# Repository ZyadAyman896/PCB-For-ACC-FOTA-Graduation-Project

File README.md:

# PCB-For-ACC-FOTA-Graduation-Project
My PCB design for our graduation's project .
## PCB Fabricated

### PCB Design

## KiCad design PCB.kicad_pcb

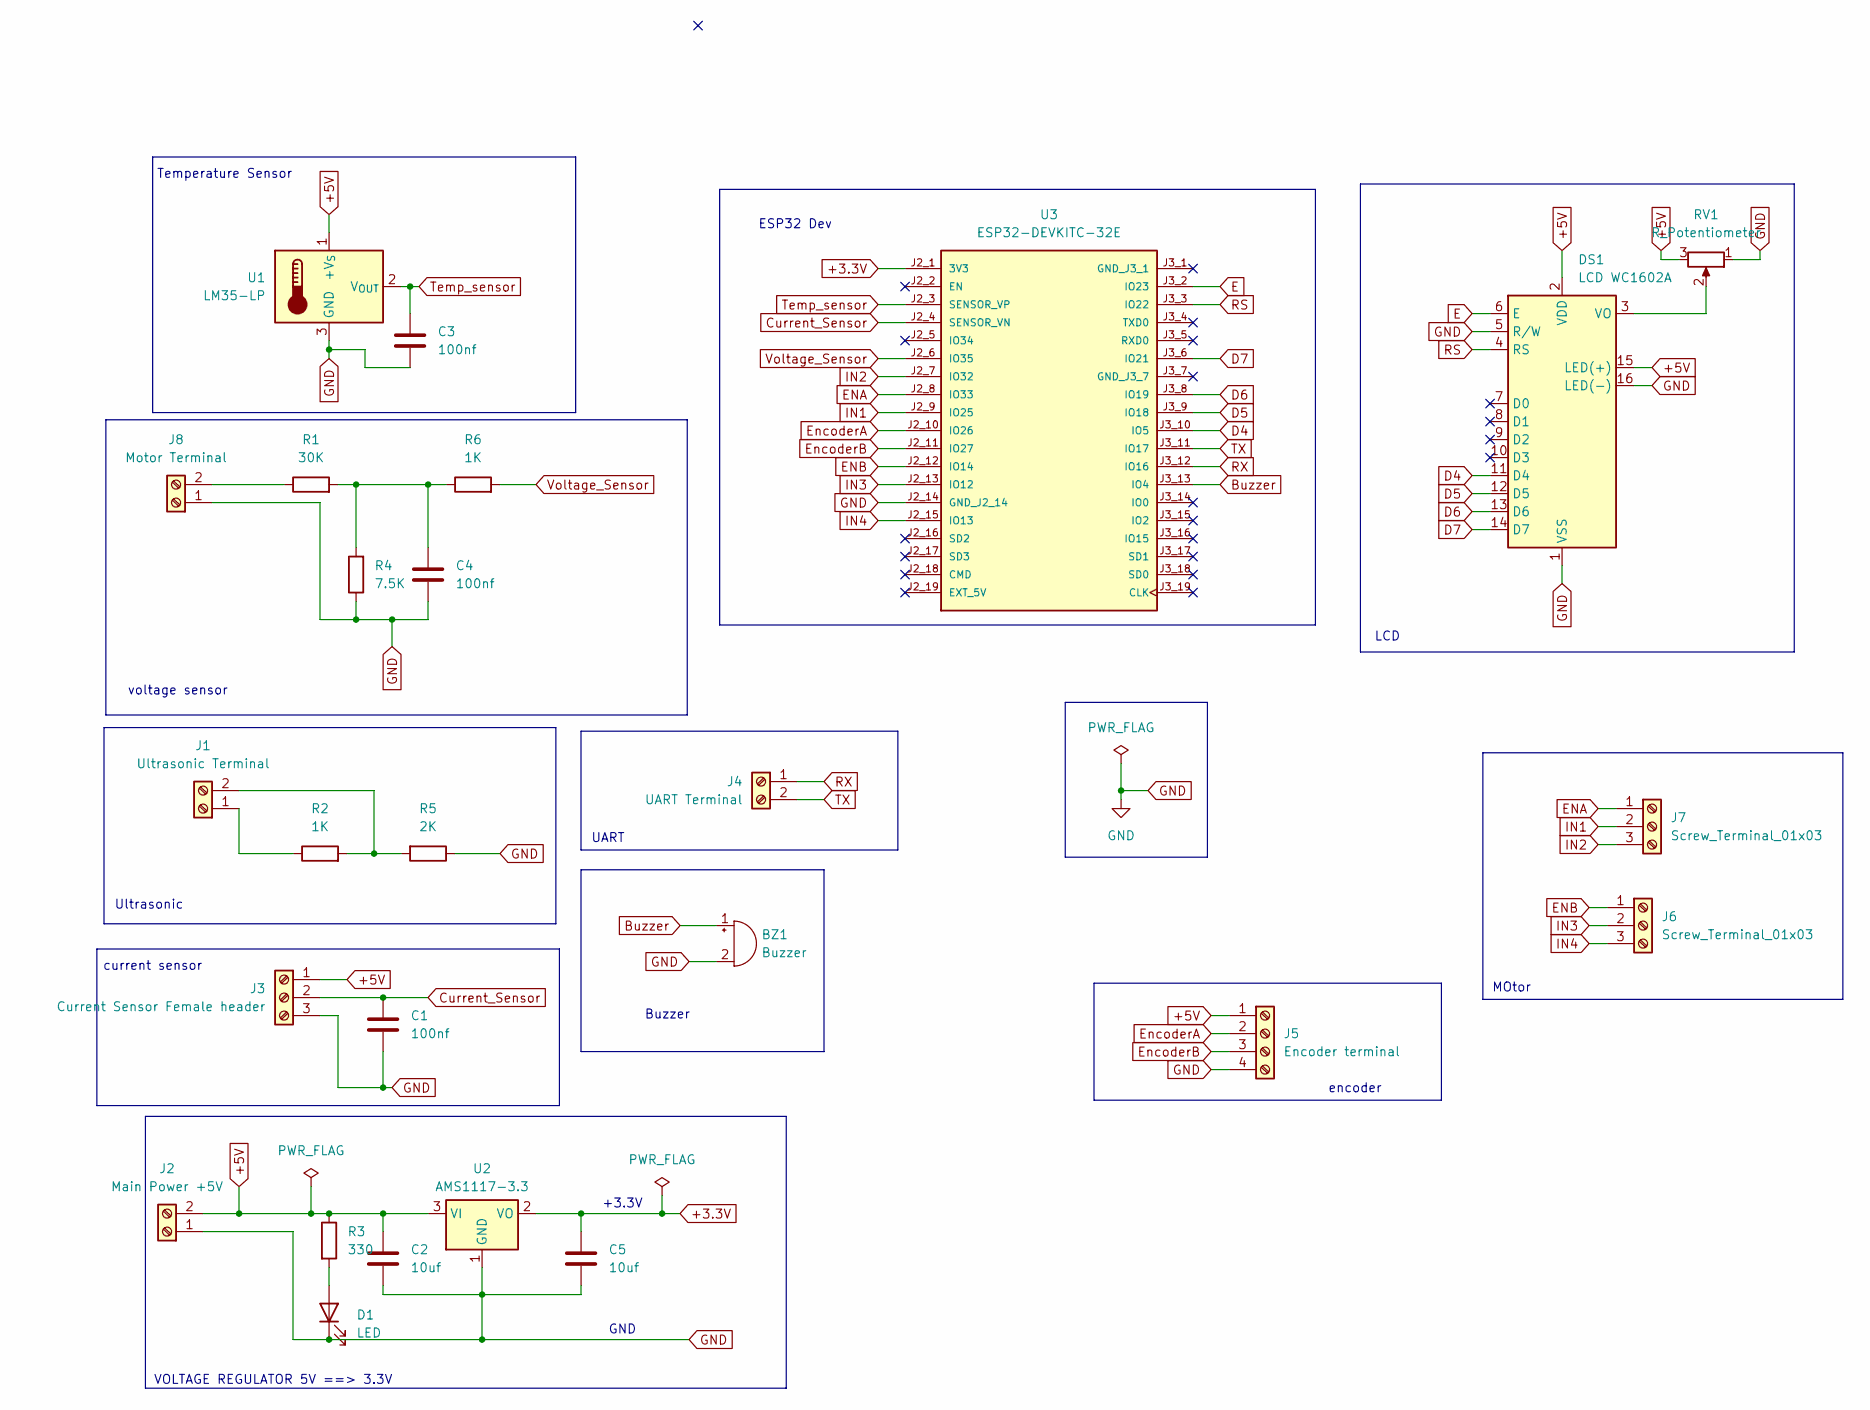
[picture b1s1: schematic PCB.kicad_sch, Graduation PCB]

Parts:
BZ1: Buzzer; Buzzer_12x9.5RM7.6
C1, C3, C4: 100nf; C_Disc_D5.0mm_W2.5mm_P5.00mm
C2, C5: 10uf; CP_Radial_D5.0mm_P2.00mm
D1: LED; LED_1206_3216Metric
DS1: LCD WC1602A; PinHeader_1x16_P2.54mm_Vertical
J1: Ultrasonic Terminal; TerminalBlock_bornier-2_P5.08mm
J2: Main Power +5V; TerminalBlock_bornier-2_P5.08mm
J3: Current Sensor Female header; PinHeader_1x03_P2.54mm_Vertical
J4: UART Terminal; TerminalBlock_bornier-2_P5.08mm
J5: Encoder terminal; TE_282837-4
J6, J7: Screw_Terminal_01x03; TE_282836-3
J8: Motor Terminal; TerminalBlock_bornier-2_P5.08mm
R1: 30K; R_Axial_DIN0207_L6.3mm_D2.5mm_P10.16mm_Horizontal
R2, R6: 1K; R_Axial_DIN0207_L6.3mm_D2.5mm_P10.16mm_Horizontal
R3: 330; R_Axial_DIN0207_L6.3mm_D2.5mm_P10.16mm_Horizontal
R4: 7.5K; R_Axial_DIN0207_L6.3mm_D2.5mm_P10.16mm_Horizontal
R5: 2K; R_Axial_DIN0207_L6.3mm_D2.5mm_P10.16mm_Horizontal
RV1: R_Potentiometer; TRIM_WH148-1A-2-18T-L20
U1: LM35-LP; TO-92_Inline
U2: AMS1117-3.3; SOT-223-3_TabPin2
U3: ESP32-DEVKITC-32E; MODULE_ESP32-DEVKITC-32E; PARTREV 1.4

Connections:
+3.3V: C5.1, U2.2 (VO), U3.J2_1 (3V3)
+5V: C2.1, DS1.2 (VDD), DS1.15 (LED(+)), J2.2, J3.1, J5.1, R3.1, RV1.3, U1.1 (+V_{S}), U2.3 (VI)
Buzzer: BZ1.1 (+), U3.J3_13 (IO4)
Current_Sensor: C1.1, J3.2, U3.J2_4 (SENSOR_VN)
D4: DS1.11 (D4), U3.J3_10 (IO5)
D5: DS1.12 (D5), U3.J3_9 (IO18)
D6: DS1.13 (D6), U3.J3_8 (IO19)
D7: DS1.14 (D7), U3.J3_6 (IO21)
E: DS1.6 (E), U3.J3_2 (IO23)
ENA: J7.1, U3.J2_8 (IO33)
ENB: J6.1, U3.J2_12 (IO14)
EncoderA: J5.2, U3.J2_10 (IO26)
EncoderB: J5.3, U3.J2_11 (IO27)
GND: BZ1.2 (-), C1.2, C2.2, C3.2, C4.2, C5.2, D1.1 (K), DS1.1 (VSS), DS1.5 (R/W), DS1.16 (LED(-)), J2.1, J3.3, J5.4, J8.1, R4.1, R5.1, RV1.1, U1.3 (GND), U2.1 (GND), U3.J2_14 (GND_J2_14)
IN1: J7.2, U3.J2_9 (IO25)
IN2: J7.3, U3.J2_7 (IO32)
IN3: J6.2, U3.J2_13 (IO12)
IN4: J6.3, U3.J2_15 (IO13)
unnamed: C4.1, R1.2, R4.2, R6.1
unnamed: D1.2 (A), R3.2
unnamed: DS1.3 (VO), RV1.2
unnamed: J1.1, R2.1
unnamed: J1.2, R2.2, R5.2
unnamed: J8.2, R1.1
RS: DS1.4 (RS), U3.J3_3 (IO22)
RX: J4.1, U3.J3_12 (IO16)
TX: J4.2, U3.J3_11 (IO17)
Temp_sensor: C3.1, U1.2 (V_{OUT}), U3.J2_3 (SENSOR_VP)
Voltage_Sensor: R6.2, U3.J2_6 (IO35)

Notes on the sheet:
Ultrasonic
encoder
+3.3V
UART
MOtor
ESP32 Dev
voltage sensor
LCD
VOLTAGE REGULATOR 5V ==> 3.3V
current sensor
GND
Buzzer
Temperature Sensor

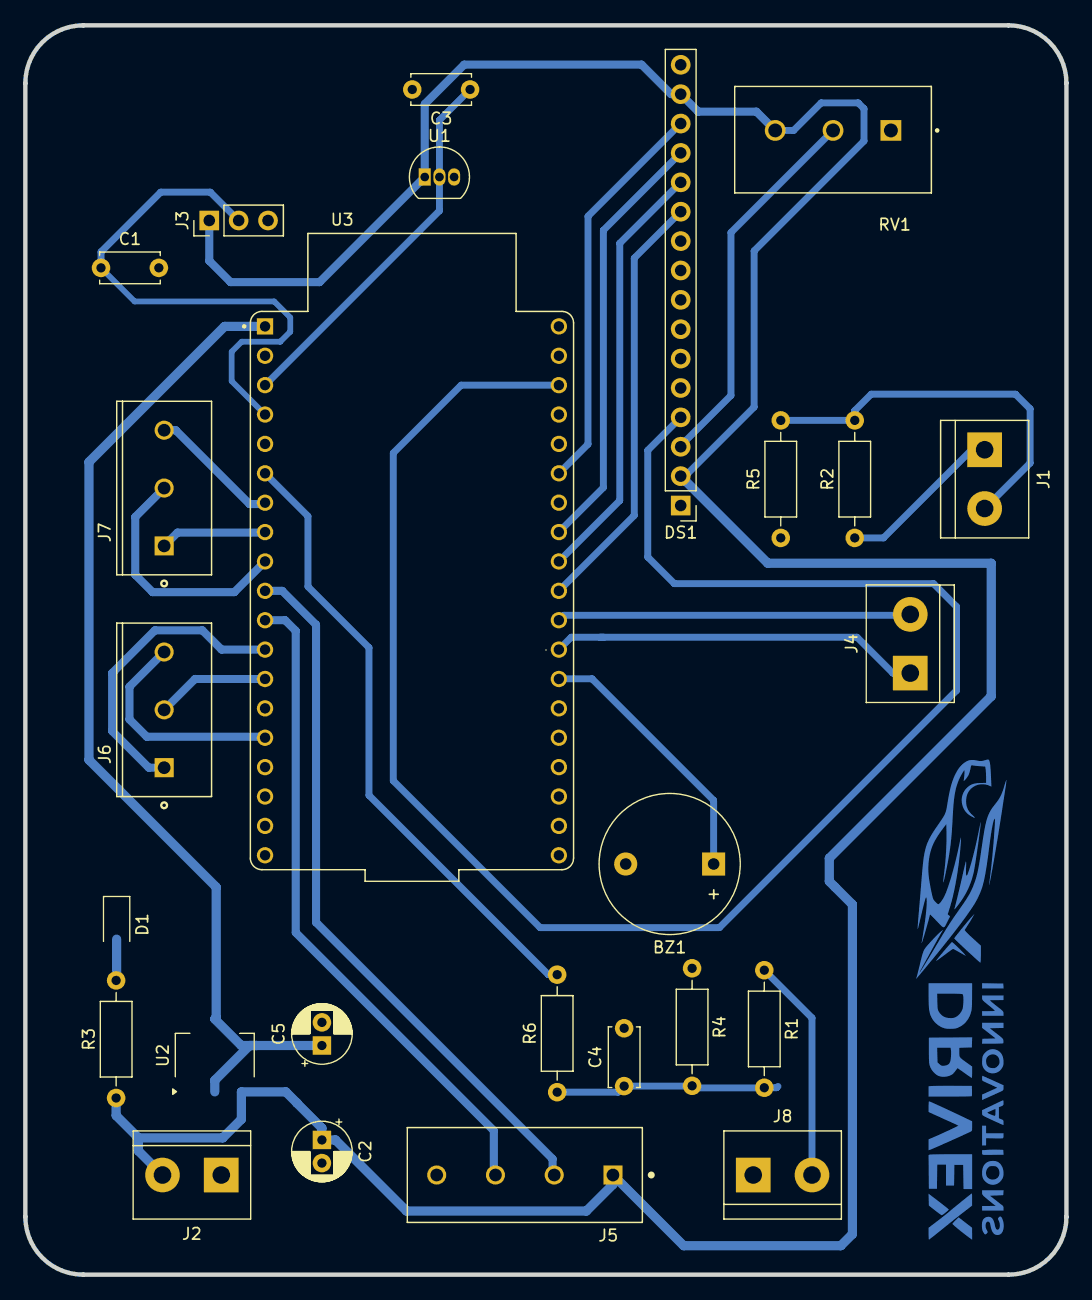
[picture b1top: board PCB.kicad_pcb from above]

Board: 2 copper layers, 90.0 x 108.0 mm, 26 parts (0 on the bottom side), 29 nets.
